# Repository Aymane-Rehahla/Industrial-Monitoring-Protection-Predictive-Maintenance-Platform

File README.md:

# Industrial Distributed Monitoring & Protection Platform

> A modular industrial monitoring and protection system built with ESP32-S3 and ESP32 using ESP-IDF.
>
> Designed for reliability, fault tolerance, and safety-critical industrial environments.

---

## Overview

This project is my graduation project and represents the largest embedded system I have designed.

The system monitors industrial electrical and environmental parameters in real time while protecting equipment through a layered safety architecture.

Unlike many academic projects, this system was designed with **industrial reliability** as the primary goal.

It combines:

- Dual ESP32 architecture
- Independent hardware watchdogs
- Redundant communication
- Modular sensor framework
- Industrial HMI
- Remote monitoring dashboard
- Real-time protection algorithms

---

# Architecture

```
                   iPad Dashboard
                  (Web Application)
                         │
                    WiFi / TCP
                         │
                 ESP32 HMI Gateway
                         │
                  Encrypted ESP-NOW
                         │
      ┌──────────────────┴──────────────────┐
      │                                     │
 ESP32-S3 Safety Node A           ESP32-S3 Safety Node B
      │                                     │
      └────────── Cross Validation ─────────┘
                     │
              Dual ATtiny85 Watchdogs
                     │
               Independent NE555 Watchdog
                     │
               Industrial Safety Relay
```

---

# Key Features

## Industrial Protection

- Three-phase voltage monitoring
- Three-phase current monitoring
- Temperature monitoring
- Humidity monitoring
- Gas detection
- RPM monitoring
- Vibration monitoring
- Relay feedback verification
- Fault logging
- Alarm management

---

## Real-Time Processing

The ESP32-S3 performs all protection-critical calculations:

- RMS calculation
- Phase sequence detection
- Phase loss detection
- Voltage imbalance
- Current imbalance
- Frequency measurement
- Locked rotor detection
- Thermal I²t model
- Shock detection
- Safety trips

The ADC hardware provides roughly 860 samples/second in total — not per phase. Reconstructing an accurate current waveform for all three phases at once meant that budget had to be shared rather than used sequentially: the sample rate is divided across the three phases so each one is still captured within the same electrical cycle, instead of measuring one phase fully before moving to the next and introducing timing skew between them.

If a condition can damage equipment...

**the ESP32 reacts immediately.**

---

## Remote Monitoring

The ESP32 Gateway serves a web application accessible from an iPad or any browser.

Features include

- Live dashboard
- Real-time sensor values
- Alarm history
- Historical trends
- Waveform visualization
- Configuration interface
- Maintenance analytics

---

# Safety Philosophy

The most important design goal was **eliminating single points of failure.**

Every protection layer assumes another layer may eventually fail.

## Layer 1 — Software

Industrial state machines

Fault handling

CRC validation

Communication verification

Configuration validation

---

## Layer 2 — Dual ESP32 Supervision

Two ESP32 controllers continuously supervise each other.

Each verifies

- communication integrity
- sensor validity
- heartbeat
- operating state

If disagreement occurs

the system enters a safe state.

---

## Layer 3 — Intelligent Hardware Watchdogs

Two ATtiny85 microcontrollers independently supervise the ESP32 controllers.

Instead of accepting a simple heartbeat,

the watchdog expects a **rolling authentication key**.

This prevents situations where a crashed processor repeatedly outputs the same pulse.

If the rolling key becomes invalid,

the watchdog assumes the firmware is malfunctioning and removes the safety relay.

---

## Layer 4 — Independent NE555 Emergency Watchdog

Even watchdogs can fail.

To eliminate this possibility, an entirely independent NE555 hardware watchdog was added.

Unlike the programmable watchdogs,

the NE555 requires no firmware.

If every controller becomes unresponsive and no valid heartbeat reaches the timer,

the NE555 automatically

- opens the safety contactor
- resets the processors
- forces the system into a safe state

This final layer is completely hardware-based and cannot be affected by firmware bugs.

---

# Contactor State Verification

Commanding the contactor to open is not the same as confirming it actually did.

Under fault current, contactor contacts can weld or stick closed — silently defeating every protection layer above while still reporting a "safe" command was issued.

To catch this, voltage and current are sensed independently on both sides of the contactor: three points upstream (supply side) and three points downstream (load side), one per phase. Comparing the two sides directly reveals the real physical state of the contactor — whether it failed to open when commanded, or is welded shut — rather than relying on the command signal alone.

---

# Modular Sensor Architecture

One design objective was allowing industrial installations to evolve without modifying firmware.

Sensors are treated as independent modules.

Each module can

- be added
- removed
- enabled
- disabled
- configured

independently.

Protection limits are configurable rather than hardcoded.

A hardware switch also selects between simple (3-phase, no neutral) and complex (3-phase + neutral) wiring configurations, so the same platform can be installed across different machine and service types without a firmware change.

This allows the same firmware to support multiple industrial installations with different requirements.

---

# Communication

## ESP-NOW

- encrypted transport
- CRC validation
- packet sequencing
- custom protocol
- low latency

---

## Gateway

The ESP32 gateway converts embedded telemetry into data suitable for the web dashboard.

---

# Technologies

- ESP-IDF
- C
- FreeRTOS
- ESP32-S3
- ESP32
- ESP-NOW
- TCP/IP
- HTML
- JavaScript
- I2C
- UART
- SPI
- ADS1115
- SHT45
- ATtiny85

---

# Project Highlights

✔ Custom communication protocol

✔ Distributed embedded architecture

✔ Modular driver framework

✔ Industrial HMI

✔ Browser-based dashboard

✔ Hardware redundancy

✔ Layered watchdog system

✔ Safety relay verification

✔ Real-time monitoring

✔ Fault logging

✔ Configurable protection system

---

# Current Status

The platform is fully operational and demonstrates

- embedded firmware
- hardware integration
- communication
- industrial HMI
- remote monitoring

Some advanced algorithms are still under active development as the project continues to evolve.

---

# Future Work

- Advanced predictive diagnostics
- PLC integration (Modbus TCP)
- CAN Bus support
- MQTT gateway
- Cloud analytics
- Machine learning maintenance assistant

---

# About Me

I'm an Industrial Electronics Engineer from Algeria passionate about

- Embedded Systems
- Firmware Development
- Industrial Automation
- Safety-Critical Software

I'm currently seeking Embedded Software, Firmware, Electronics and Industrial Automation opportunities with visa sponsorship.

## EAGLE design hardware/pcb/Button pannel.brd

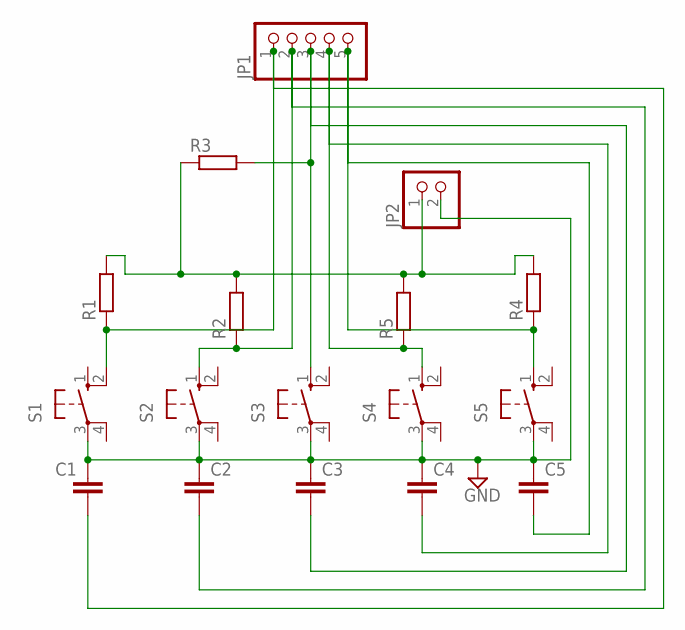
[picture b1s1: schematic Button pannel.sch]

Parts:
C1, C2, C3, C4, C5: C-EU025-025X050; C025-025X050
JP1: PINHD-1X5; 1X05
JP2: PINHD-1X2; 1X02
R1, R2, R3, R4, R5: R-EU_0204/7; 0204/7
S1, S2, S3, S4, S5: 40-XX; B3F-40XX

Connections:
GND: C1.1, C2.1, C3.1, C4.1, C5.1, JP2.2, S1.3, S2.3, S3.3, S4.3, S5.3
unnamed: C2.2, JP1.2, R2.1, S2.1 (S)
unnamed: C1.2, JP1.1, R1.1, S1.2 (S1)
unnamed: C3.2, JP1.3, R3.2, S3.1 (S)
unnamed: C4.2, JP1.4, R5.1, S4.1 (S)
unnamed: C5.2, JP1.5, R4.1, S5.1 (S)
unnamed: JP2.1, R1.2, R2.2, R3.1, R4.2, R5.2

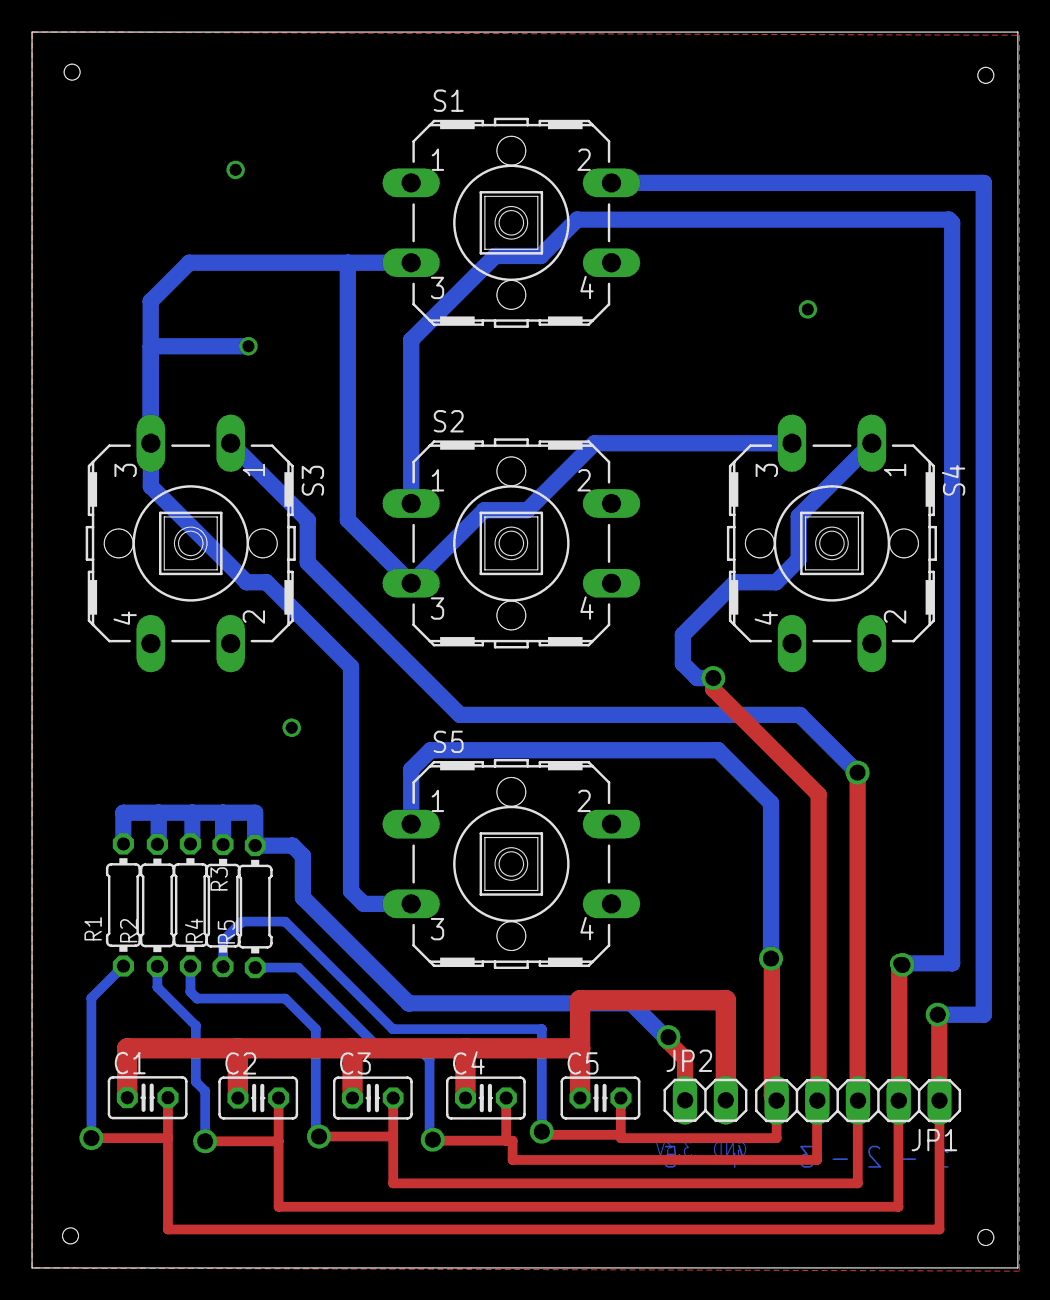
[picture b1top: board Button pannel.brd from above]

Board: 2 copper layers, 61.5 x 77.1 mm, 17 parts (0 on the bottom side), 7 nets.

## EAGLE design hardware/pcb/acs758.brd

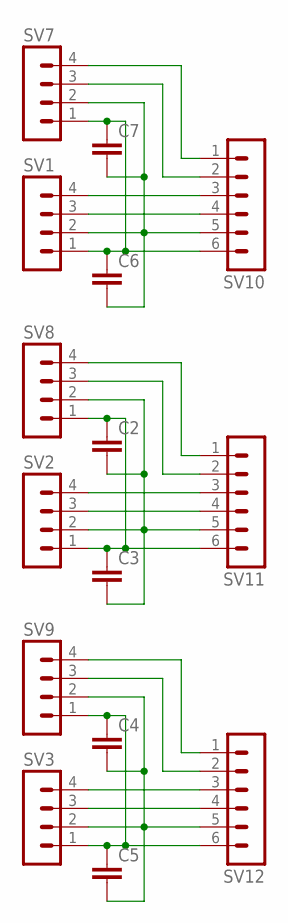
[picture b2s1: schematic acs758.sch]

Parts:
C2, C3, C4, C5, C6, C7: C-EU025-025X050; C025-025X050
SV1, SV2, SV3, SV7, SV8, SV9: MA04-1
SV10, SV11, SV12: MA06-1

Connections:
unnamed: SV1.3, SV10.4
unnamed: C4.1, C5.1, SV3.1, SV9.1, SV12.6
unnamed: SV2.3, SV11.4
unnamed: SV3.3, SV12.4
unnamed: SV3.4, SV12.3
unnamed: SV9.3, SV12.2
unnamed: SV9.4, SV12.1
unnamed: C2.1, C3.1, SV2.1, SV8.1, SV11.6
unnamed: SV2.4, SV11.3
unnamed: SV8.3, SV11.2
unnamed: SV8.4, SV11.1
unnamed: C6.1, C7.1, SV1.1, SV7.1, SV10.6
unnamed: SV1.4, SV10.3
unnamed: C6.2, C7.2, SV1.2, SV7.2, SV10.5
unnamed: C2.2, C3.2, SV2.2, SV8.2, SV11.5
unnamed: SV7.3, SV10.2
unnamed: SV7.4, SV10.1
unnamed: C4.2, C5.2, SV3.2, SV9.2, SV12.5

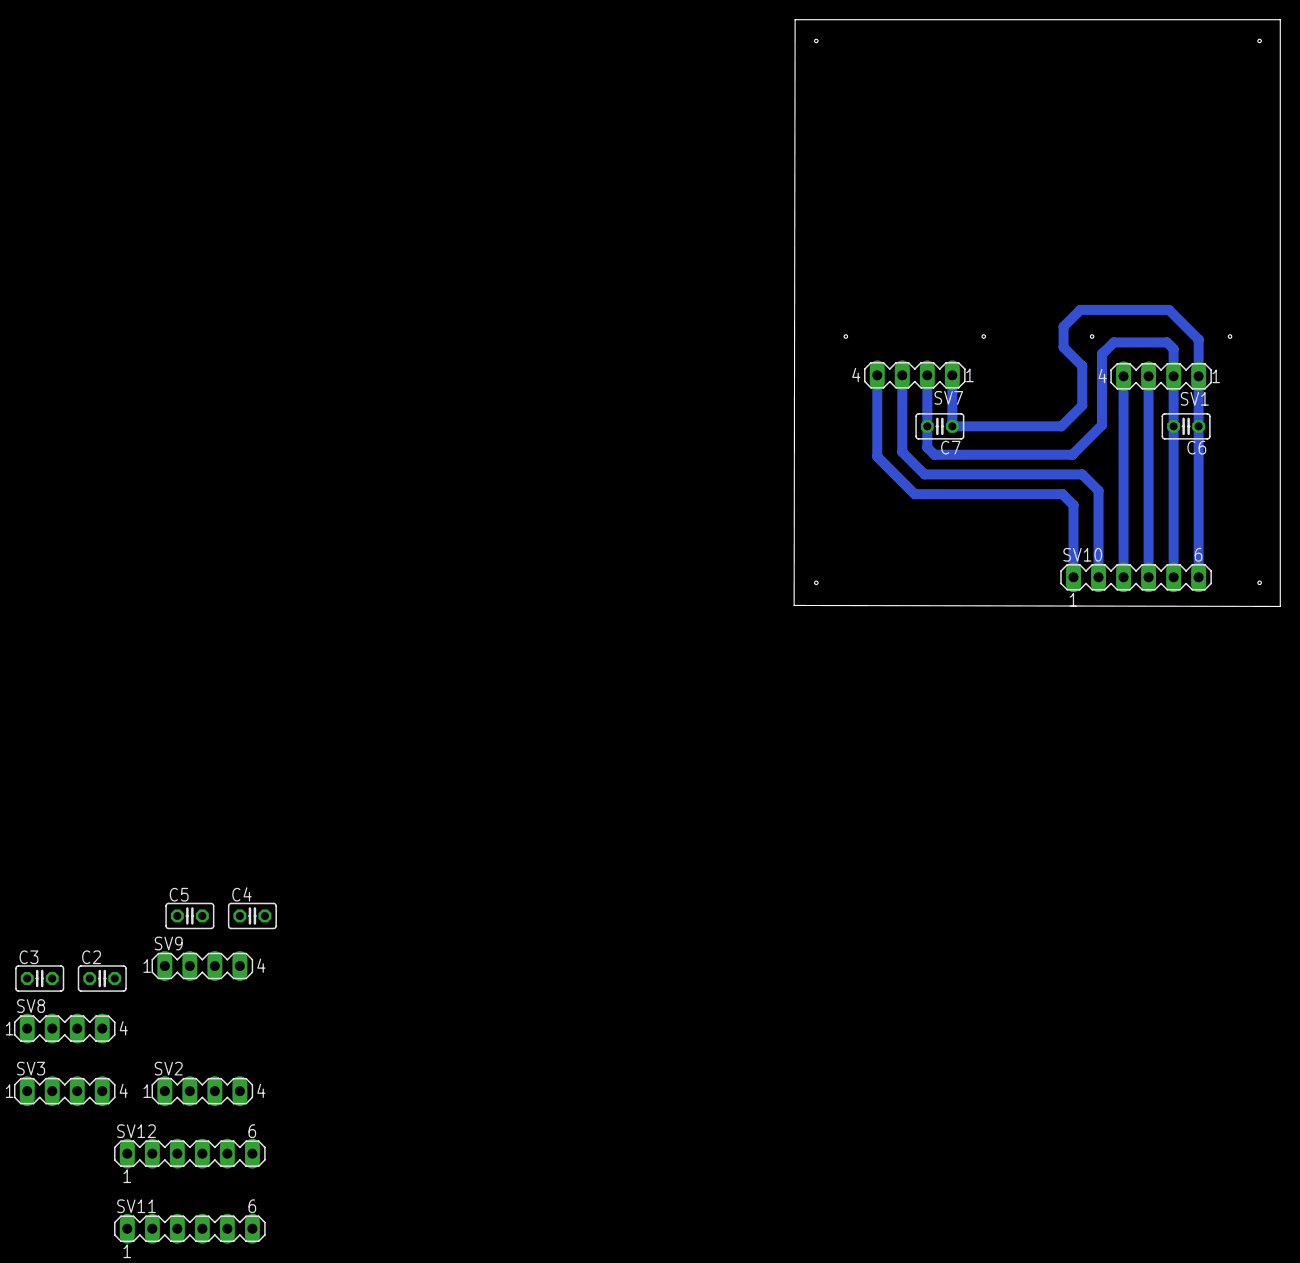
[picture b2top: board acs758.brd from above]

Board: 2 copper layers, 49.3 x 59.6 mm, 15 parts (0 on the bottom side), 18 nets.

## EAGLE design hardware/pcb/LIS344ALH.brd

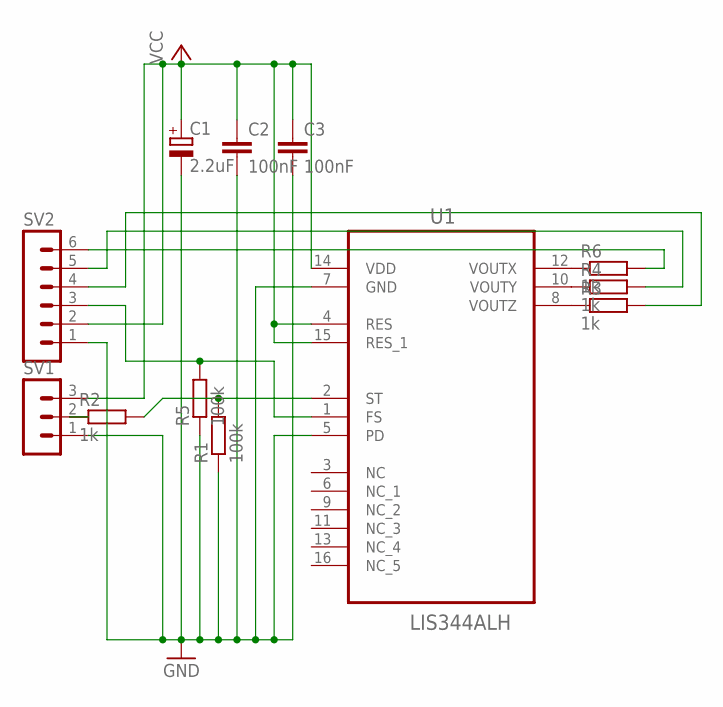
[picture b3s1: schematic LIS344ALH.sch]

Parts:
C1: 2.2uF; E2,5-6E
C2, C3: 100nF; C2.5-2
R1, R5: 100k; 0204/7
R2, R3, R4, R6: 1k; 0204/7
SV1: MA03-1
SV2: MA06-1
U1: LIS344ALH; LGA16R65P4X4_400X400X160

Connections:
GND: C1.-, C2.2, C3.2, R1.1, R5.1, SV1.1, SV2.1, U1.5 (PD), U1.7 (GND)
unnamed: R6.1, U1.12 (VOUTX)
unnamed: R4.1, U1.10 (VOUTY)
unnamed: R3.1, U1.8 (VOUTZ)
unnamed: R6.2, SV2.6
unnamed: R4.2, SV2.5
unnamed: R3.2, SV2.4
unnamed: R2.1, SV1.2
unnamed: R1.2, R2.2, U1.2 (ST)
unnamed: R5.2, SV2.3, U1.1 (FS)
VCC: C1.+, C2.1, C3.1, SV1.3, SV2.2, U1.4 (RES), U1.14 (VDD), U1.15 (RES_1)

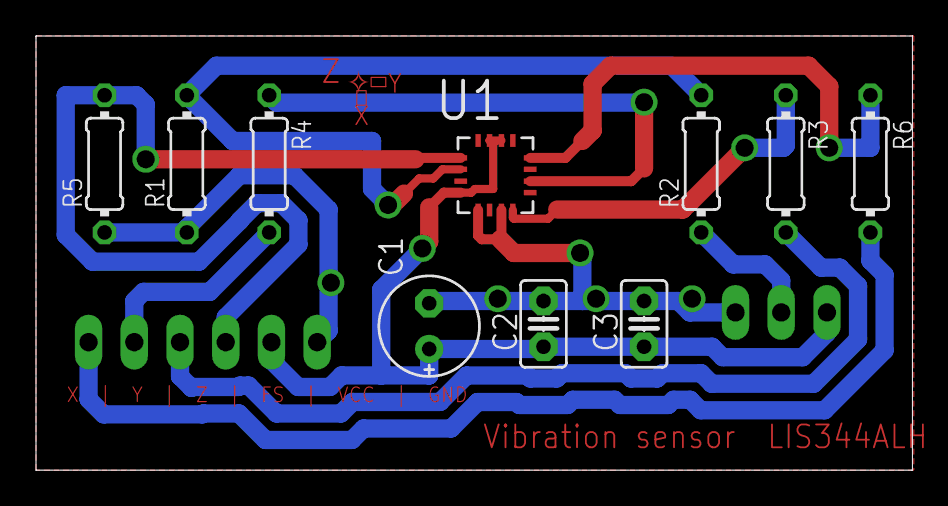
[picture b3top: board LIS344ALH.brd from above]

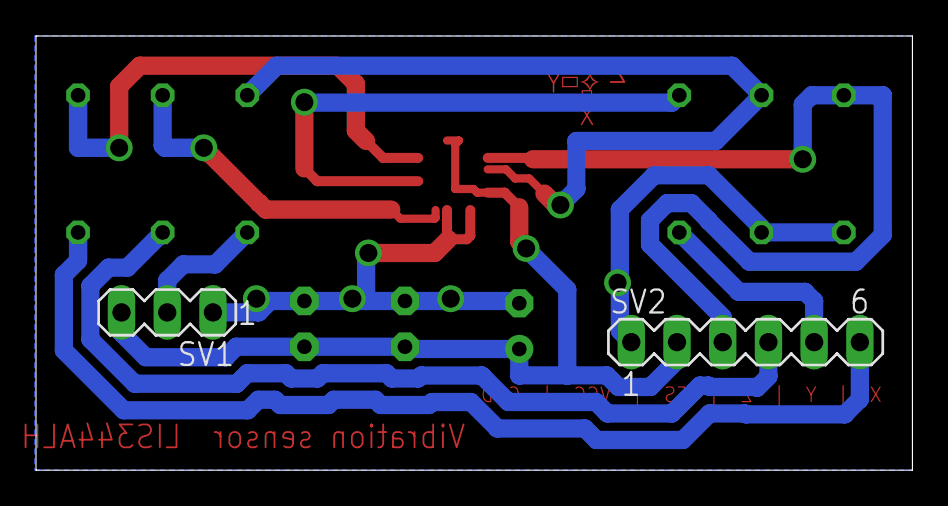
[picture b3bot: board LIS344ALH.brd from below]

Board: 2 copper layers, 48.7 x 24.1 mm, 12 parts (2 on the bottom side), 11 nets.

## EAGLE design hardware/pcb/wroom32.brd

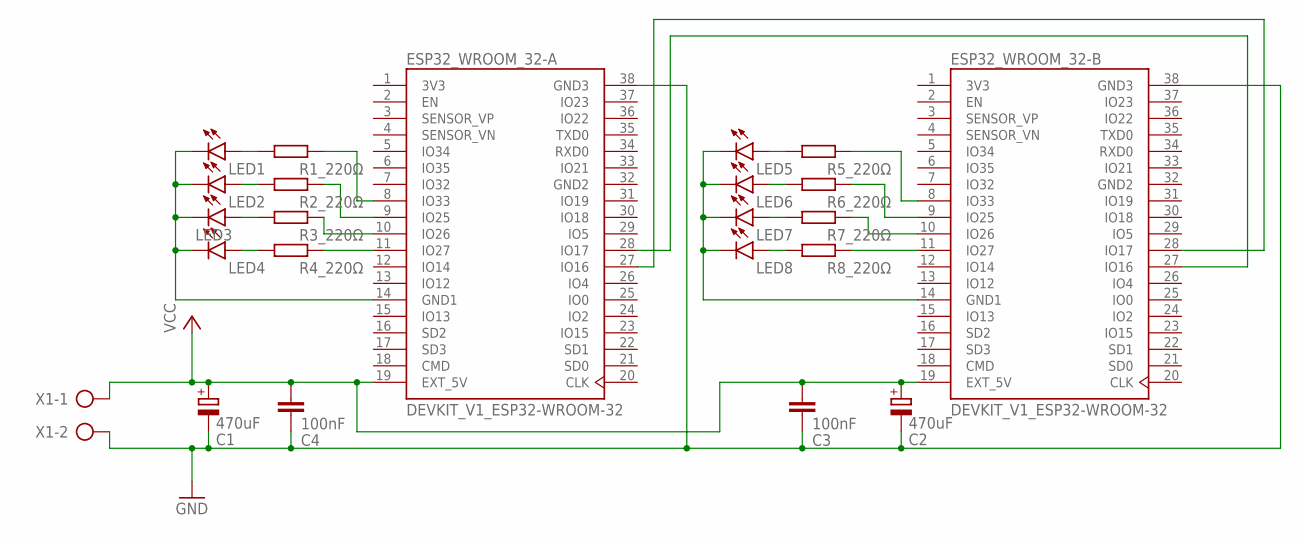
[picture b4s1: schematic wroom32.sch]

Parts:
C1, C2: 470uF; E2,5-7
C3, C4: 100nF; C025-024X044
ESP32_WROOM_32-A, ESP32_WROOM_32-B: DEVKIT_V1_ESP32-WROOM-32; MODULE_DEVKIT_V1_ESP32-WROOM-32
LED1, LED2, LED3, LED4, LED5, LED6, LED7, LED8: TLLG4400; LED3MM
R1_220Ω, R2_220Ω, R3_220Ω, R4_220Ω, R5_220Ω, R6_220Ω, R7_220Ω, R8_220Ω: R-EU_0207/10; 0207/10
X1: AK500/2-H

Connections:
3V3: ESP32_WROOM_32-A.1 (3V3), ESP32_WROOM_32-B.1 (3V3)
GND: C1.-, C2.-, C3.2, C4.2, ESP32_WROOM_32-A.38 (GND3), ESP32_WROOM_32-B.38 (GND3), X1.2
GND2: ESP32_WROOM_32-A.32 (GND2), ESP32_WROOM_32-B.32 (GND2)
unnamed: ESP32_WROOM_32-A.28 (IO17), ESP32_WROOM_32-B.27 (IO16)
unnamed: ESP32_WROOM_32-A.27 (IO16), ESP32_WROOM_32-B.28 (IO17)
unnamed: ESP32_WROOM_32-B.14 (GND1), LED5.K (C), LED6.K (C), LED7.K (C), LED8.K (C)
unnamed: ESP32_WROOM_32-A.14 (GND1), LED1.K (C), LED2.K (C), LED3.K (C), LED4.K (C)
unnamed: LED1.A, R1_220Ω.1
unnamed: LED2.A, R2_220Ω.1
unnamed: LED3.A, R3_220Ω.1
unnamed: LED4.A, R4_220Ω.1
unnamed: ESP32_WROOM_32-A.11 (IO27), R4_220Ω.2
unnamed: ESP32_WROOM_32-A.10 (IO26), R3_220Ω.2
unnamed: ESP32_WROOM_32-A.9 (IO25), R2_220Ω.2
unnamed: ESP32_WROOM_32-A.8 (IO33), R1_220Ω.2
unnamed: ESP32_WROOM_32-B.8 (IO33), R5_220Ω.2
unnamed: ESP32_WROOM_32-B.9 (IO25), R6_220Ω.2
unnamed: ESP32_WROOM_32-B.10 (IO26), R7_220Ω.2
unnamed: ESP32_WROOM_32-B.11 (IO27), R8_220Ω.2
unnamed: LED8.A, R8_220Ω.1
unnamed: LED7.A, R7_220Ω.1
unnamed: LED6.A, R6_220Ω.1
unnamed: LED5.A, R5_220Ω.1
VCC: C1.+, C2.+, C3.1, C4.1, ESP32_WROOM_32-A.19 (EXT_5V), ESP32_WROOM_32-B.19 (EXT_5V), X1.1

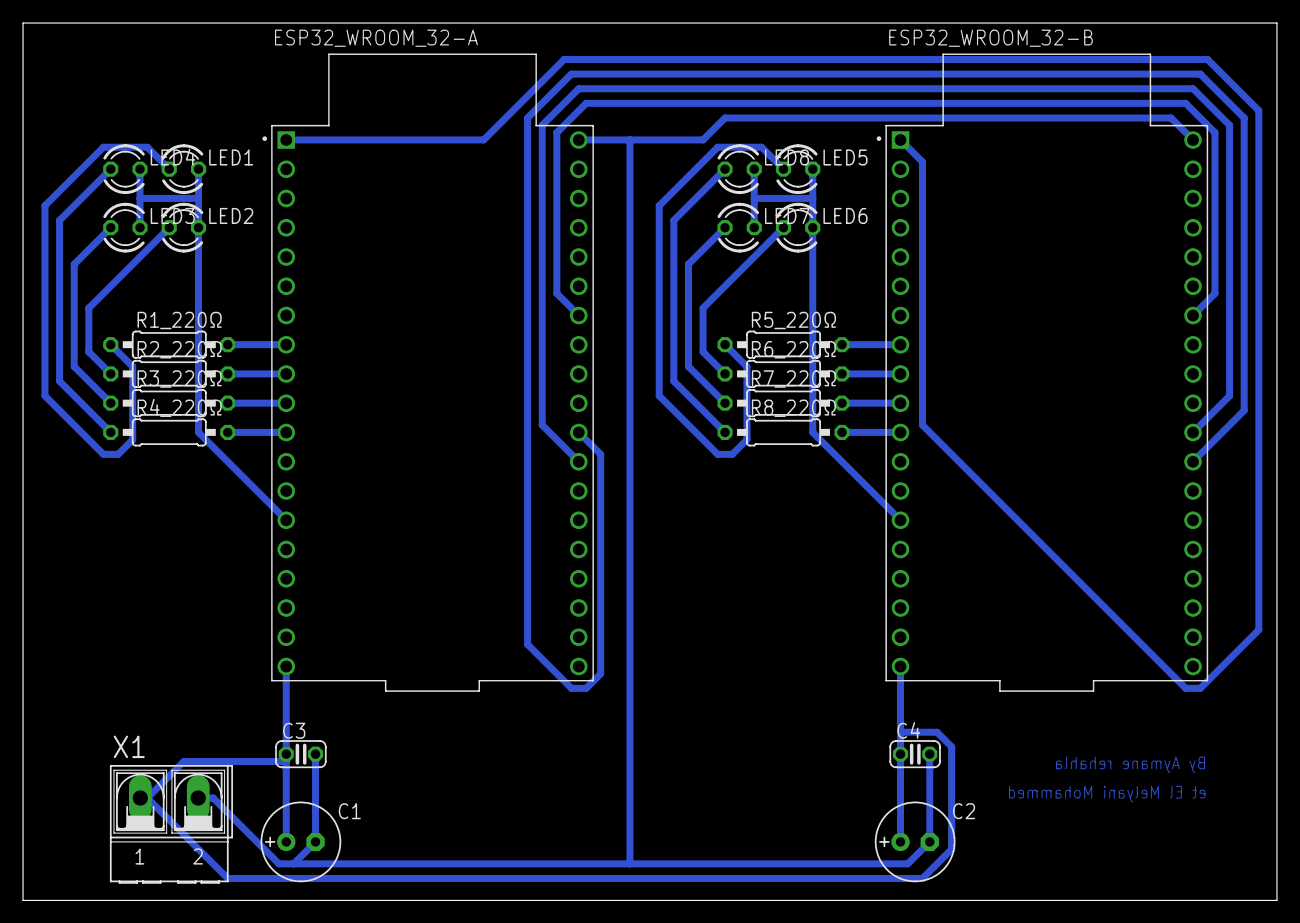
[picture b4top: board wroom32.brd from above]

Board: 2 copper layers, 108.9 x 76.2 mm, 23 parts (0 on the bottom side), 24 nets.

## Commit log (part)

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2026-02-11 havnt tested yet
